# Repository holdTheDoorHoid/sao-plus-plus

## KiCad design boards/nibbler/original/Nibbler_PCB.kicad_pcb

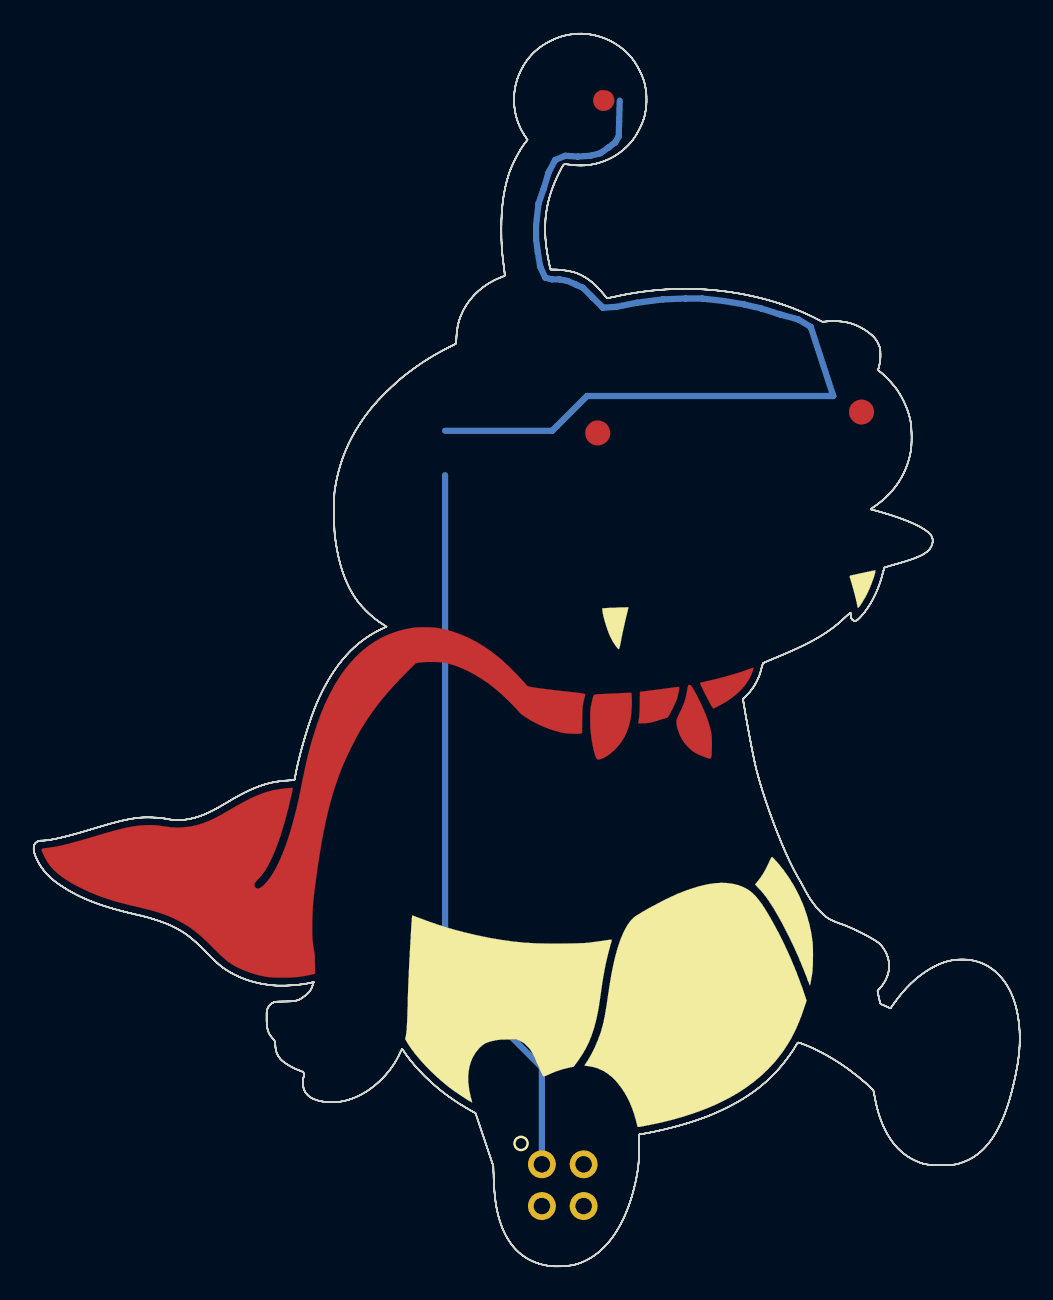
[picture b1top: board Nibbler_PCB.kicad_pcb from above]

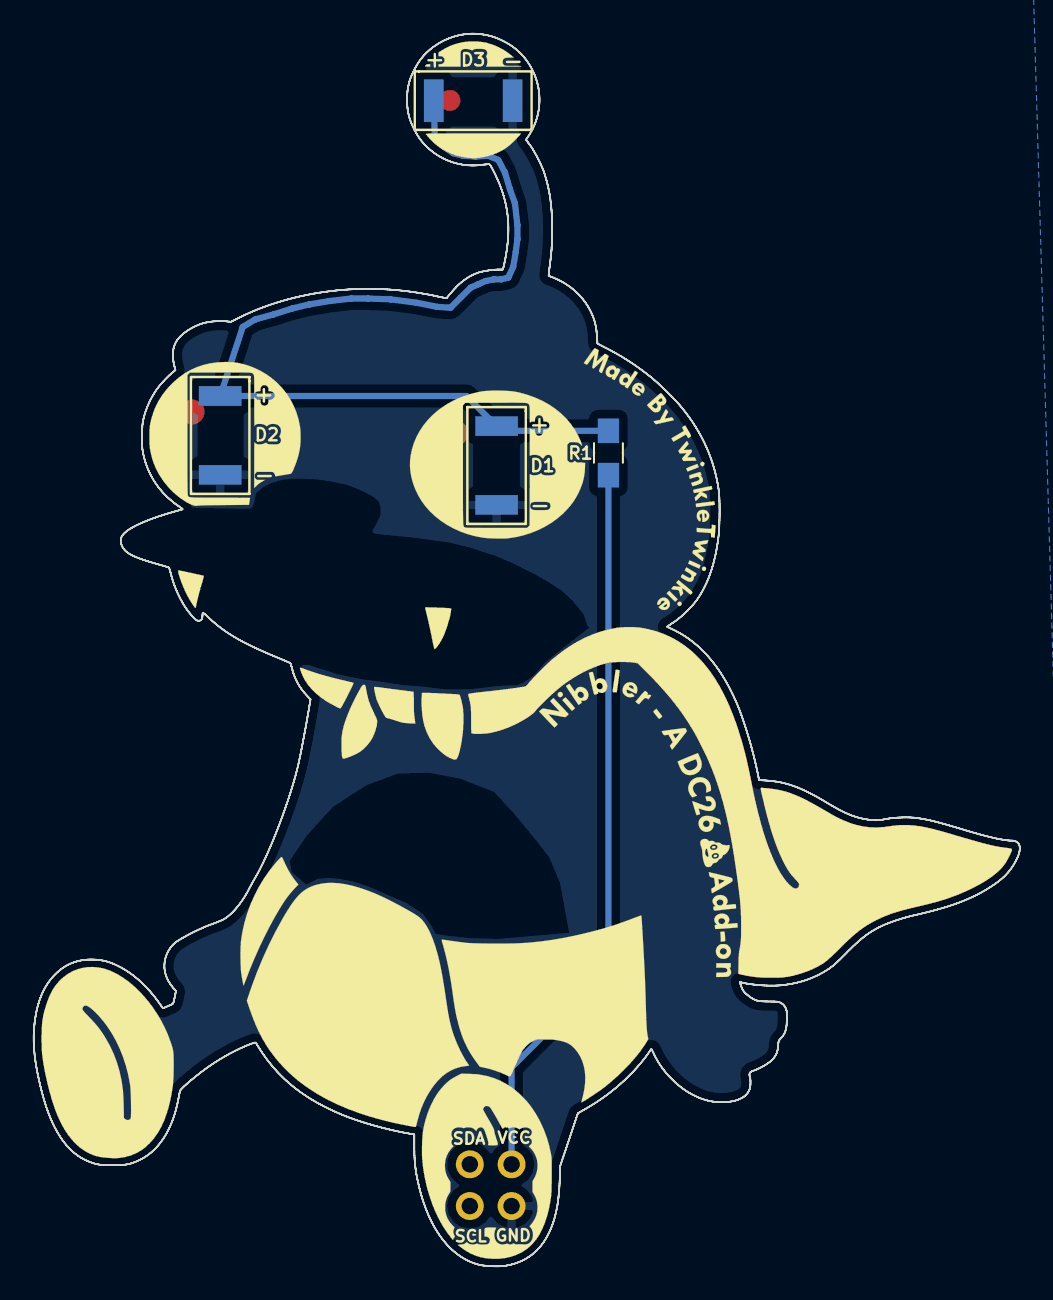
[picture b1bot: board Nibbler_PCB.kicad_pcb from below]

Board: 2 copper layers, 60.0 x 75.0 mm, 7 parts (4 on the bottom side), 3 nets.

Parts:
B.Mask: LOGO
D1, D2, D3: LED; LED_OSRAM_TOPLED_LxT776
F.Silk: LOGO
R1: R; R_0805_HandSoldering
X1: Badgelife_shitty_connector; Badgelife-Shitty-2x2

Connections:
unnamed: D1.1, D2.1, D3.1, X1.2
unnamed: D1.2, D2.2, D3.2, R1.2
unnamed: R1.1, X1.1

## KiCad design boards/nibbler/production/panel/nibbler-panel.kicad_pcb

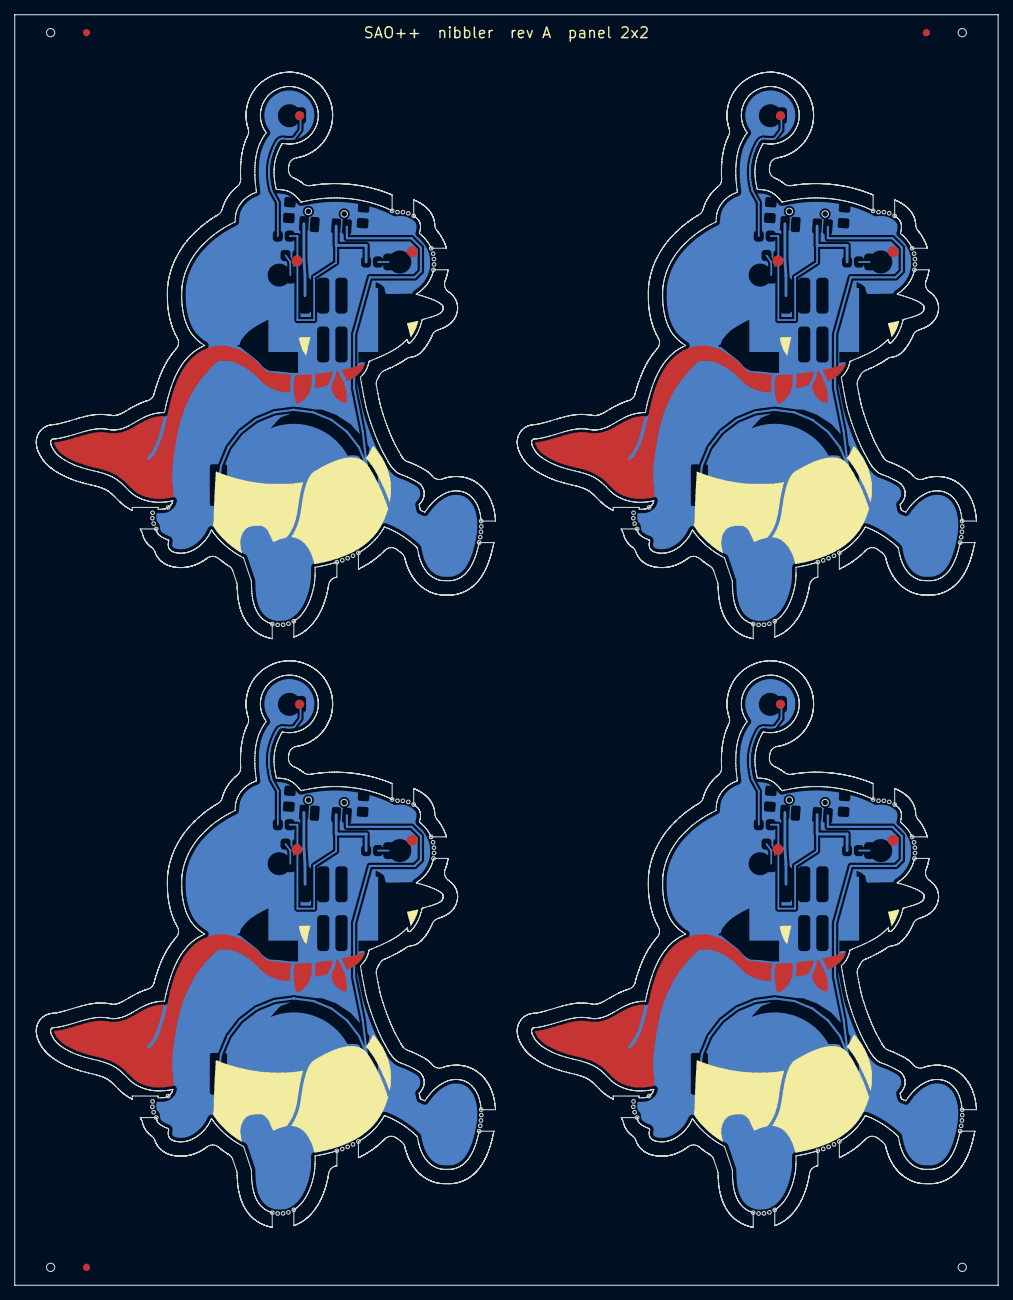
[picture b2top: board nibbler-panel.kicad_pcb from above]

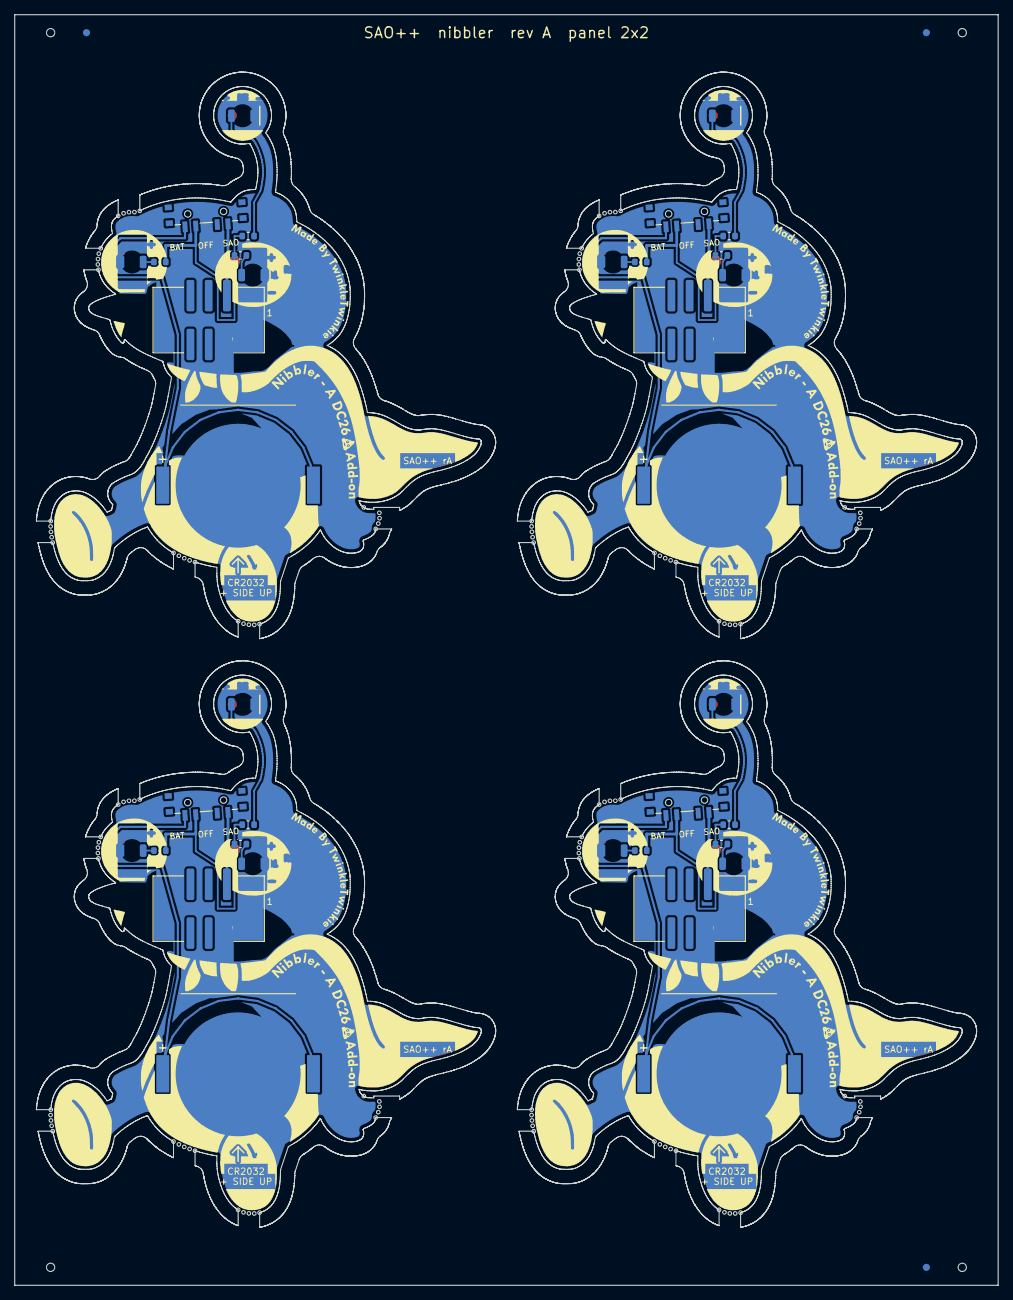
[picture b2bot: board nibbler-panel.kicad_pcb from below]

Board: 2 copper layers, 137.0 x 177.0 mm, 44 parts (36 on the bottom side), 28 nets.

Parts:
B.Mask, B.Mask#2, B.Mask#3, B.Mask#4: LOGO
BT101, BT201, BT301, BT401: CR2032; SAOPP_BAT-01_CR2032_SMD_TE_BAT-HLD-001
D101, D102, D103, D201, D202, D203, D301, D302, D303, D401, D402, D403: white; SAOPP_LED-10_1206_ReverseMount_ThroughBoard
F.Silk, F.Silk#2, F.Silk#3, F.Silk#4: LOGO
J101, J201, J301, J401: SAO v1.69bis; SAOPP_CONN-01_BoxHeader_2x03_P2.54mm_SMD_XFCN_BH254VS-6P
R101, R102, R103, R201, R202, R203, R301, R302, R303, R401, R402, R403: 1.3k; SAOPP_R_0603_1608Metric
SW101, SW201, SW301, SW401: SAO / OFF / BAT; SAOPP_SW-01_Slide_SP3T_CK_PCM13SMTR

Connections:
B2-GND: BT201.2, D201.1, D202.1, D203.1, J201.2
B2-LED1_A: D201.2, R201.2
B2-LED2_A: D202.2, R202.2
B2-LED3_A: D203.2, R203.2
B2-VBAT: BT201.1, SW201.4
B2-VLOAD: R201.1, R202.1, R203.1, SW201.3
B2-VSAO: J201.1, SW201.1
B3-GND: BT301.2, D301.1, D302.1, D303.1, J301.2
B3-LED1_A: D301.2, R301.2
B3-LED2_A: D302.2, R302.2
B3-LED3_A: D303.2, R303.2
B3-VBAT: BT301.1, SW301.4
B3-VLOAD: R301.1, R302.1, R303.1, SW301.3
B3-VSAO: J301.1, SW301.1
B4-GND: BT401.2, D401.1, D402.1, D403.1, J401.2
B4-LED1_A: D401.2, R401.2
B4-LED2_A: D402.2, R402.2
B4-LED3_A: D403.2, R403.2
B4-VBAT: BT401.1, SW401.4
B4-VLOAD: R401.1, R402.1, R403.1, SW401.3
B4-VSAO: J401.1, SW401.1
GND: BT101.2, D101.1, D102.1, D103.1, J101.2
LED1_A: D101.2, R101.2
LED2_A: D102.2, R102.2
LED3_A: D103.2, R103.2
VBAT: BT101.1, SW101.4
VLOAD: R101.1, R102.1, R103.1, SW101.3
VSAO: J101.1, SW101.1

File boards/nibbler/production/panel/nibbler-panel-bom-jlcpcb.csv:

Comment,Designator,Footprint,LCSC Part #
CR2032,"BT101,BT201,BT301,BT401",SAOPP_BAT-01_CR2032_SMD_TE_BAT-HLD-001,C7501066
white,"D101,D102,D103,D201,D202,D203,D301,D302,D303,D401,D402,D403",SAOPP_LED-10_1206_ReverseMount_ThroughBoard,C575513
SAO v1.69bis,"J101,J201,J301,J401",SAOPP_CONN-01_BoxHeader_2x03_P2.54mm_SMD_XFCN_BH254VS-6P,C492445
1.3k,"R101,R102,R103,R201,R202,R203,R301,R302,R303,R401,R402,R403",SAOPP_R_0603_1608Metric,C22767
SAO / OFF / BAT,"SW101,SW201,SW301,SW401",SAOPP_SW-01_Slide_SP3T_CK_PCM13SMTR,C221842

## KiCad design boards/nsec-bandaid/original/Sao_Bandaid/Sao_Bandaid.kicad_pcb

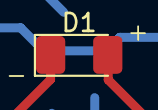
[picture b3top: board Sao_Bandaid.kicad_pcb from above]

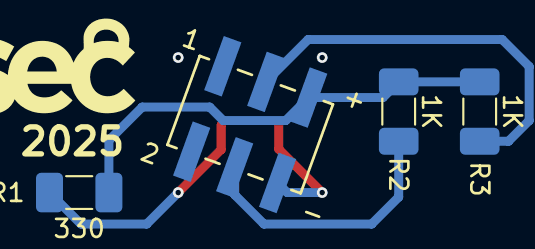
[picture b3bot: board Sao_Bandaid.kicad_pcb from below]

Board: 2 copper layers, 5 parts (4 on the bottom side), 5 nets.

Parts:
D1: LED; LED_1206_3216Metric_Pad1.42x1.75mm_HandSolder
J1: SAO Connector SMD
R1: 330; R_1206_3216Metric_Pad1.30x1.75mm_HandSolder
R2, R3: 1K; R_1206_3216Metric_Pad1.30x1.75mm_HandSolder

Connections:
+3V3: J1.5 (3V3), R1.1, R2.2, R3.2
GND: D1.1 (K), J1.6 (GND)
unnamed: D1.2 (A), R1.2
unnamed: J1.4 (SCL), R2.1
unnamed: J1.3 (SDA), R3.1

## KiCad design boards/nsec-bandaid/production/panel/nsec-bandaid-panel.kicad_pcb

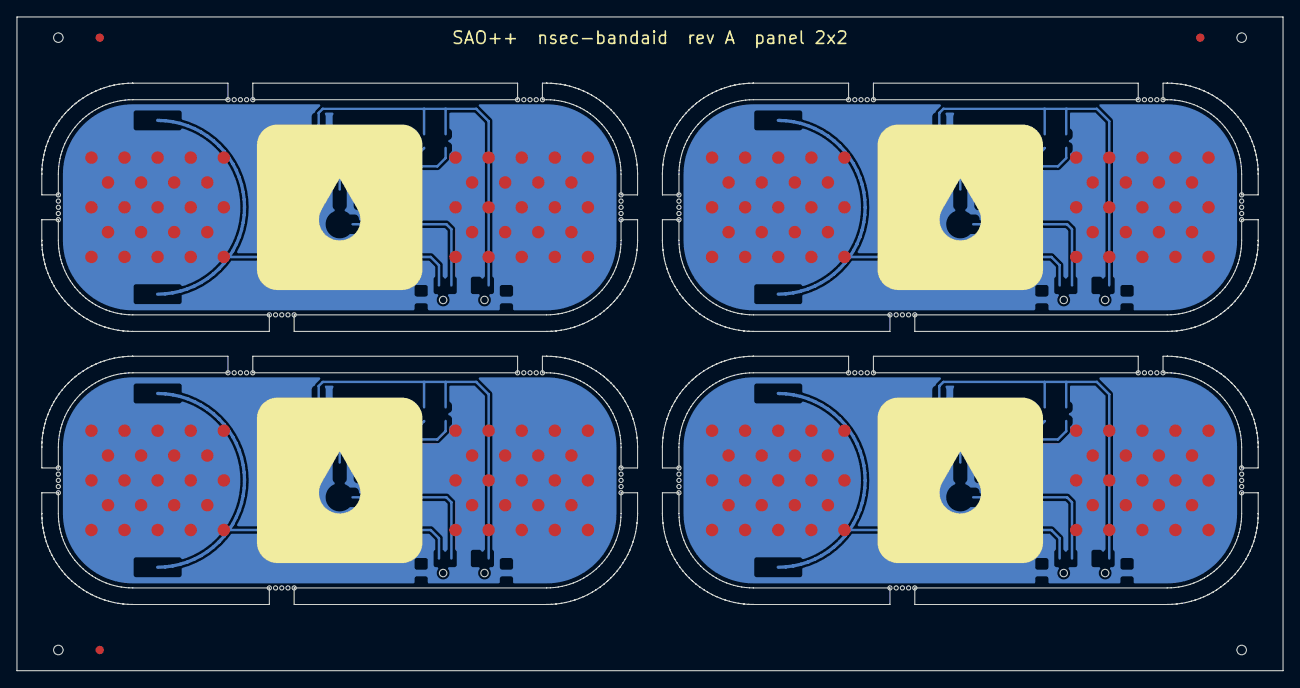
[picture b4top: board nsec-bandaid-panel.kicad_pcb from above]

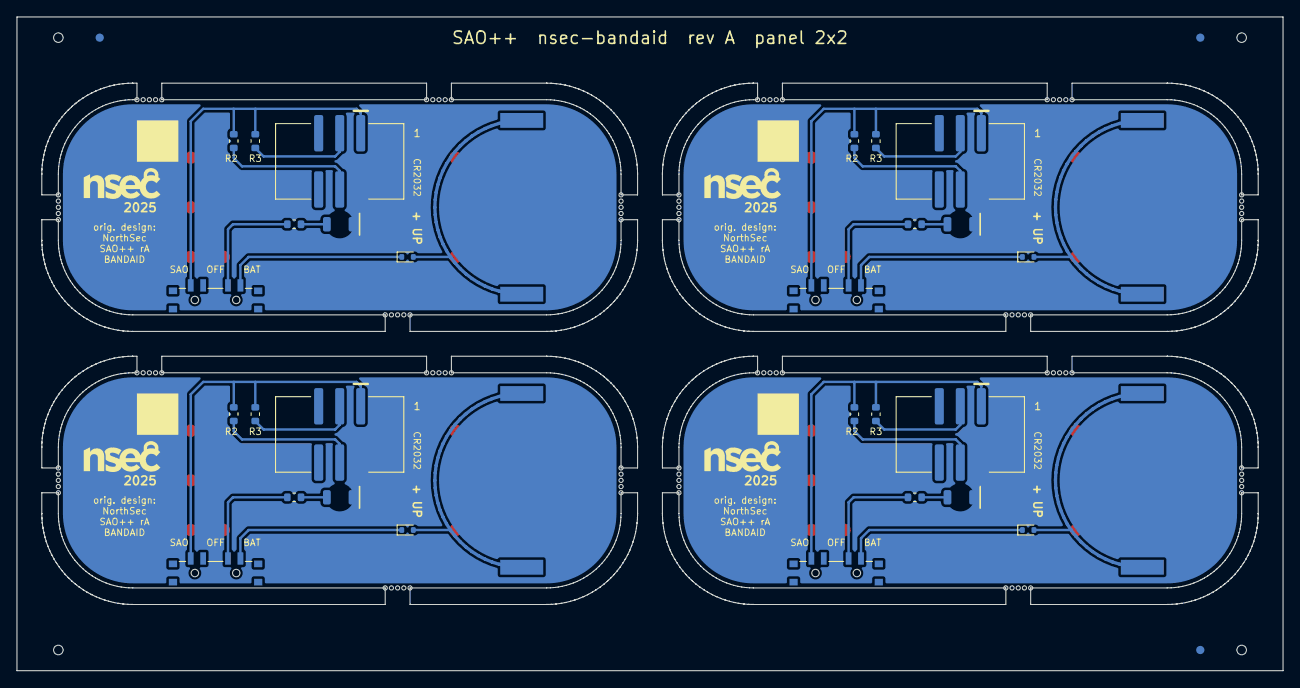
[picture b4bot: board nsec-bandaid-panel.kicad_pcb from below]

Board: 2 copper layers, 153.0 x 79.0 mm, 32 parts (32 on the bottom side), 32 nets.

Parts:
BT101, BT201, BT301, BT401: CR2032; SAOPP_BAT-01_CR2032_SMD_TE_BAT-HLD-001
D101, D201, D301, D401: red; SAOPP_LED-10_1206_ReverseMount_ThroughBoard
D102, D202, D302, D402: RB751S40; D_SOD-523
J101, J201, J301, J401: SAO v1.69bis; SAOPP_CONN-01_BoxHeader_2x03_P2.54mm_SMD_XFCN_BH254VS-6P
R101, R201, R301, R401: 1.3k; SAOPP_R_0603_1608Metric
R102, R103, R202, R203, R302, R303, R402, R403: 1.3k NOT FITTED; SAOPP_R_0603_1608Metric
SW101, SW201, SW301, SW401: SAO / OFF / BAT; SAOPP_SW-01_Slide_SP3T_CK_PCM13SMTR

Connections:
B2-GND: BT201.2, D201.1, J201.2
B2-LED_A: D201.2, R201.2
B2-SCL: J201.4, R202.2
B2-SDA: J201.3, R203.2
B2-VBAT: BT201.1, D202.2
B2-VCELL: D202.1, SW201.4
B2-VLOAD: R201.1, SW201.3
B2-VSAO: J201.1, R202.1, R203.1, SW201.1
B3-GND: BT301.2, D301.1, J301.2
B3-LED_A: D301.2, R301.2
B3-SCL: J301.4, R302.2
B3-SDA: J301.3, R303.2
B3-VBAT: BT301.1, D302.2
B3-VCELL: D302.1, SW301.4
B3-VLOAD: R301.1, SW301.3
B3-VSAO: J301.1, R302.1, R303.1, SW301.1
B4-GND: BT401.2, D401.1, J401.2
B4-LED_A: D401.2, R401.2
B4-SCL: J401.4, R402.2
B4-SDA: J401.3, R403.2
B4-VBAT: BT401.1, D402.2
B4-VCELL: D402.1, SW401.4
B4-VLOAD: R401.1, SW401.3
B4-VSAO: J401.1, R402.1, R403.1, SW401.1
GND: BT101.2, D101.1, J101.2
LED_A: D101.2, R101.2
SCL: J101.4, R102.2
SDA: J101.3, R103.2
VBAT: BT101.1, D102.2
VCELL: D102.1, SW101.4
VLOAD: R101.1, SW101.3
VSAO: J101.1, R102.1, R103.1, SW101.1

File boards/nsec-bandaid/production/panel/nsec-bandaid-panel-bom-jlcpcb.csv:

Comment,Designator,Footprint,LCSC Part #
CR2032,"BT101,BT201,BT301,BT401",SAOPP_BAT-01_CR2032_SMD_TE_BAT-HLD-001,C7501066
red,"D101,D201,D301,D401",SAOPP_LED-10_1206_ReverseMount_ThroughBoard,C125107
RB751S40,"D102,D202,D302,D402",D_SOD-523,C232576
SAO v1.69bis,"J101,J201,J301,J401",SAOPP_CONN-01_BoxHeader_2x03_P2.54mm_SMD_XFCN_BH254VS-6P,C492445
1.3k,"R101,R201,R301,R401",SAOPP_R_0603_1608Metric,C22767
SAO / OFF / BAT,"SW101,SW201,SW301,SW401",SAOPP_SW-01_Slide_SP3T_CK_PCM13SMTR,C221842

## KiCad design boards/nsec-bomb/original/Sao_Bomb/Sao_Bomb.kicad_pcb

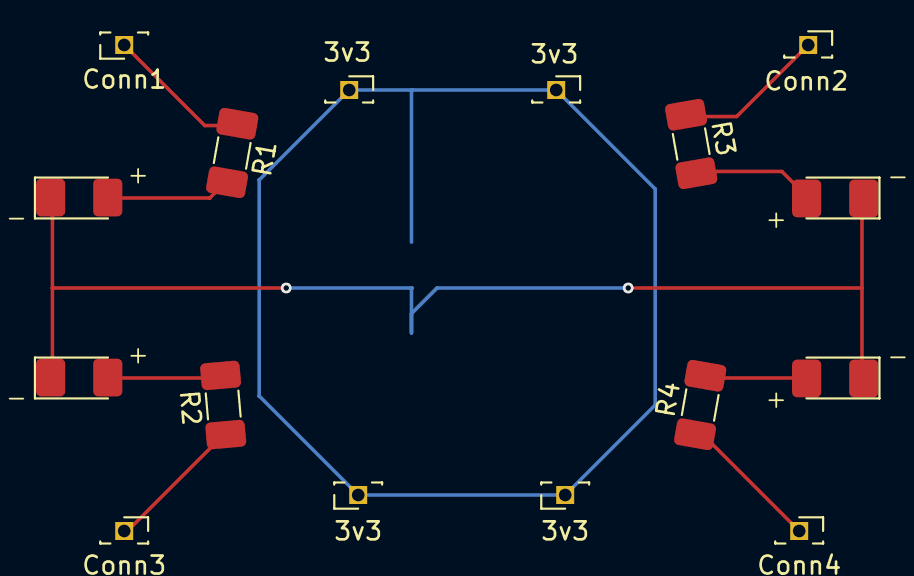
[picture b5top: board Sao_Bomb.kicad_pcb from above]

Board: 2 copper layers, 17 parts (1 on the bottom side), 10 nets.

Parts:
D1, D2, D3, D4: LED; LED_1206_3216Metric_Pad1.42x1.75mm_HandSolder
J1: SAO Connector SMD
J2, J3, J4, J5, J6, J7, J8, J9: Conn_01x01_Socket; PinSocket_1x01_P1.27mm_Vertical
R1, R2, R3, R4: 330; R_1206_3216Metric_Pad1.30x1.75mm_HandSolder

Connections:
+3V3: J1.5 (3V3), J2.1, J4.1, J6.1, J8.1
GND: D1.1 (K), D2.1 (K), D3.1 (K), D4.1 (K), J1.6 (GND)
unnamed: D1.2 (A), R1.2
unnamed: D2.2 (A), R2.2
unnamed: D3.2 (A), R3.2
unnamed: D4.2 (A), R4.2
unnamed: J3.1, R1.1
unnamed: J5.1, R2.1
unnamed: J7.1, R3.1
unnamed: J9.1, R4.1
